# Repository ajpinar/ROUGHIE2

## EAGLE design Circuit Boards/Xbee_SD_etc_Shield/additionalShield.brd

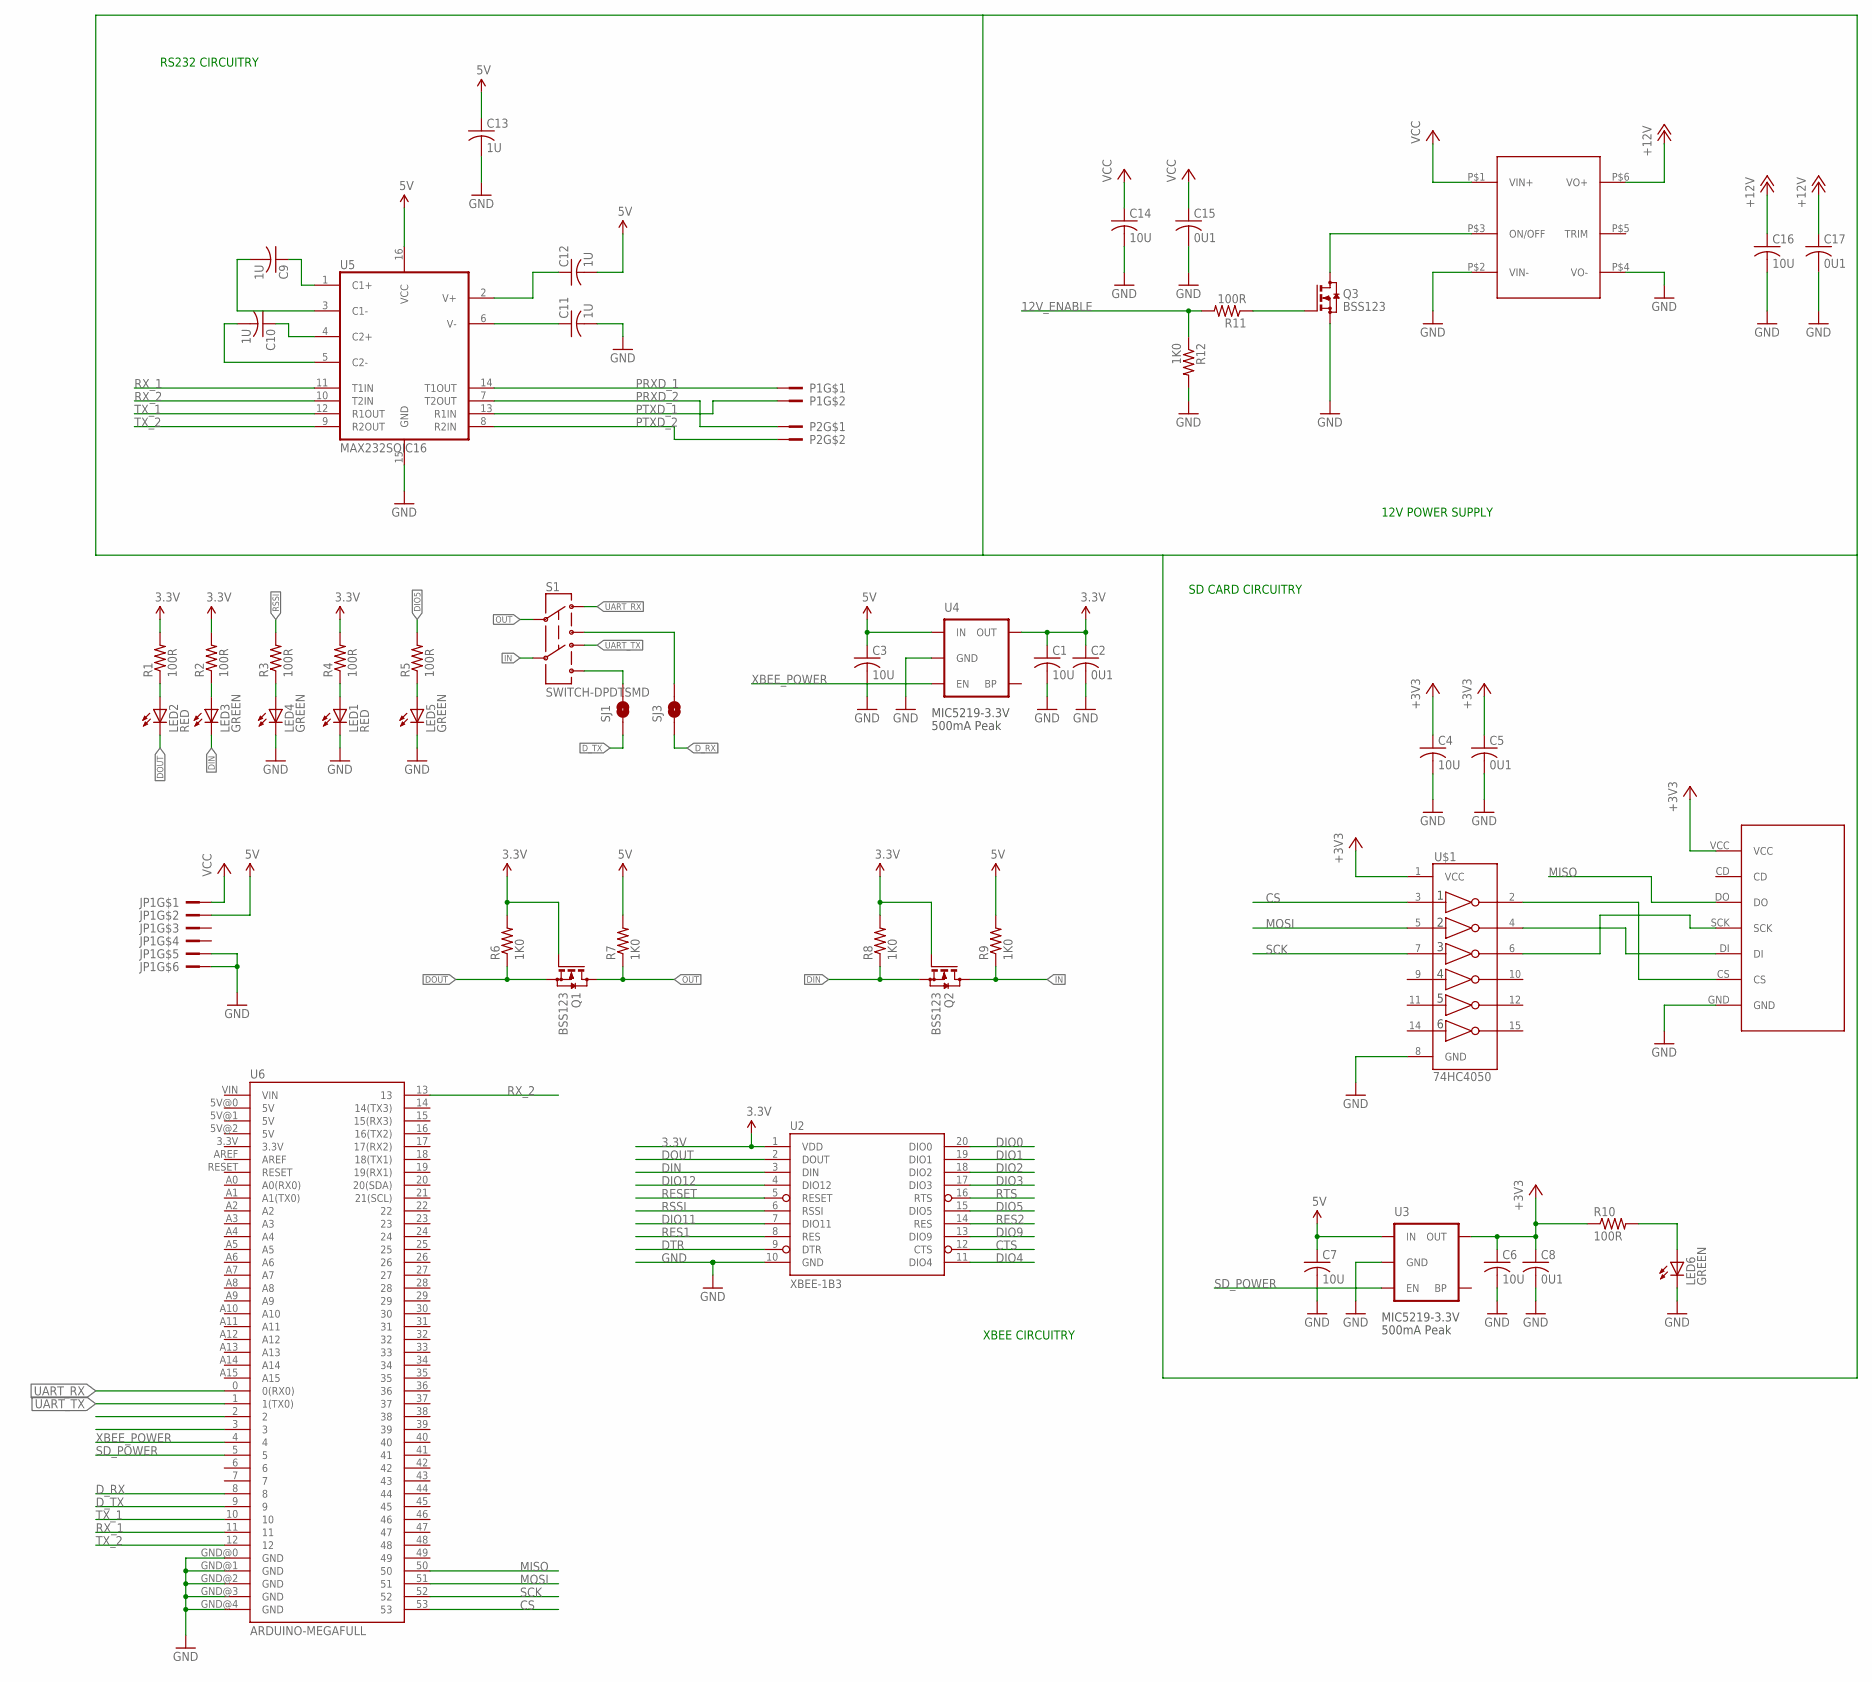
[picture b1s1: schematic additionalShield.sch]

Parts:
C1, C3, C4, C6, C7, C14, C16: 10U; C1210K
C2, C5, C8, C15, C17: 0U1; C1210K
C9, C10, C11, C12, C13: 1U; C1210K
JP1: 6PIN2ROWARDUINO
LED1, LED2: RED; CHIPLED_1206
LED3, LED4, LED5, LED6: GREEN; CHIPLED_1206
P1, P2: DF3A-2P-2DSA
Q1, Q2, Q3: BSS123; SOT23
R1, R2, R3, R4, R5, R10, R11: 100R; R1206
R6, R7, R8, R9, R12: 1K0; R1206
S1: SWITCH-DPDTSMD; AYZ0202
SJ1: D_TX; SJ_2S
SJ3: D_RX; SJ_2S
U2: XBEE-1B3; XBEE-SMD
U3, U4: V_REG_LDOSMD; SOT23-5
U5: MAX232SOIC16; SO016
U6: ARDUINO-MEGAFULL; ARDUINO_MEGA
U$1: 74HC4050; SO16
U$5: SD_BREAKOUT
U$11: SHHD001A3B41Z

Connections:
3.3V: C1.1, C2.1, Q1.1 (G), Q2.1 (G), R1.2, R2.2, R4.2, R6.2, R8.2, U2.1 (VDD), U4.5 (OUT)
5V: C3.1, C7.1, C12.2, C13.1, JP1.P$2, R7.2, R9.2, U3.1 (IN), U4.1 (IN), U5.16 (VCC)
12V_ENABLE: R11.2, R12.1
+3V3: C4.1, C5.1, C6.1, C8.1, R10.1, U3.5 (OUT), U$1.1 (VCC), U$5.VCC
+12V: C16.1, C17.1, U$11.P$6 (VO+)
CS: U6.53, U$1.3 (1A)
CTS: U2.12 (CTS)
DIN: LED3.C, Q2.2 (S), R8.1, U2.3 (DIN)
DIO0: U2.20 (DIO0)
DIO1: U2.19 (DIO1)
DIO2: U2.18 (DIO2)
DIO3: U2.17 (DIO3)
DIO4: U2.11 (DIO4)
DIO5: R5.2, U2.15 (DIO5)
DIO9: U2.13 (DIO9)
DIO11: U2.7 (DIO11)
DIO12: U2.4 (DIO12)
DOUT: LED2.C, Q1.2 (S), R6.1, U2.2 (DOUT)
DTR: U2.9 (DTR)
D_RX: SJ3.1, U6.8
D_TX: SJ1.1, U6.9
GND: C1.2, C2.2, C3.2, C4.2, C5.2, C6.2, C7.2, C8.2, C11.2, C13.2, C14.2, C15.2, C16.2, C17.2, JP1.P$5, JP1.P$6, LED1.C, LED4.C, LED5.C, LED6.C, Q3.2 (S), R12.2, U2.10 (GND), U3.2 (GND), U4.2 (GND), U5.15 (GND), U6.GND@0 (GND), U6.GND@1 (GND), U6.GND@2 (GND), U6.GND@3 (GND), U6.GND@4 (GND), U$1.8 (GND), U$5.GND, U$11.P$2 (VIN-), U$11.P$4 (VO-)
IN: Q2.3 (D), R9.1, S1.5
MISO: U6.50, U$5.DO
MOSI: U6.51, U$1.5 (2A)
unnamed: LED2.A, R1.1
unnamed: LED4.A, R3.1
unnamed: LED3.A, R2.1
unnamed: LED6.A, R10.2
unnamed: U$1.2 (1Y), U$5.CS
unnamed: U$1.4 (2Y), U$5.DI
unnamed: U$1.6 (3Y), U$5.SCK
unnamed: C9.1, U5.1 (C1+)
unnamed: C9.2, U5.3 (C1-)
unnamed: C10.1, U5.4 (C2+)
unnamed: C10.2, U5.5 (C2-)
unnamed: C11.1, U5.6 (V-)
unnamed: C12.1, U5.2 (V+)
unnamed: Q3.1 (G), R11.1
unnamed: Q3.3 (D), U$11.P$3 (ON/OFF)
unnamed: LED1.A, R4.1
unnamed: LED5.A, R5.1
unnamed: S1.6, SJ1.2
unnamed: S1.3, SJ3.2
OUT: Q1.3 (D), R7.1, S1.2
PRXD_1: P1.P$1, U5.14 (T1OUT)
PRXD_2: P2.P$1, U5.7 (T2OUT)
PTXD_1: P1.P$2, U5.13 (R1IN)
PTXD_2: P2.P$2, U5.8 (R2IN)
RES1: U2.8 (RES)
RES2: U2.14 (RES)
RESET: U2.5 (RESET)
RSSI: R3.2, U2.6 (RSSI)
RTS: U2.16 (RTS)
RX_1: U5.11 (T1IN), U6.11
RX_2: U5.10 (T2IN), U6.13
SCK: U6.52, U$1.7 (3A)
SD_POWER: U3.3 (EN), U6.5
TX_1: U5.12 (R1OUT), U6.10
TX_2: U5.9 (R2OUT), U6.12
UART_RX: S1.1, U6.0 (0(RX0))
UART_TX: S1.4, U6.1 (1(TX0))
VCC: C14.1, C15.1, JP1.P$1, U$11.P$1 (VIN+)
XBEE_POWER: U4.3 (EN), U6.4

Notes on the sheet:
500mA Peak
MIC5219-3.3V
XBEE CIRCUITRY
12V POWER SUPPLY
SD CARD CIRCUITRY
RS232 CIRCUITRY

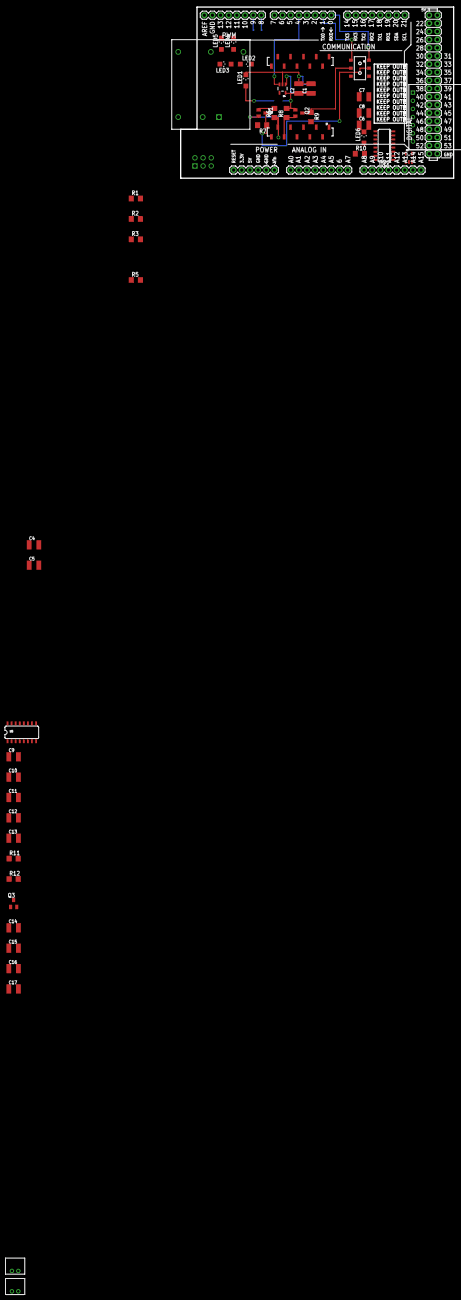
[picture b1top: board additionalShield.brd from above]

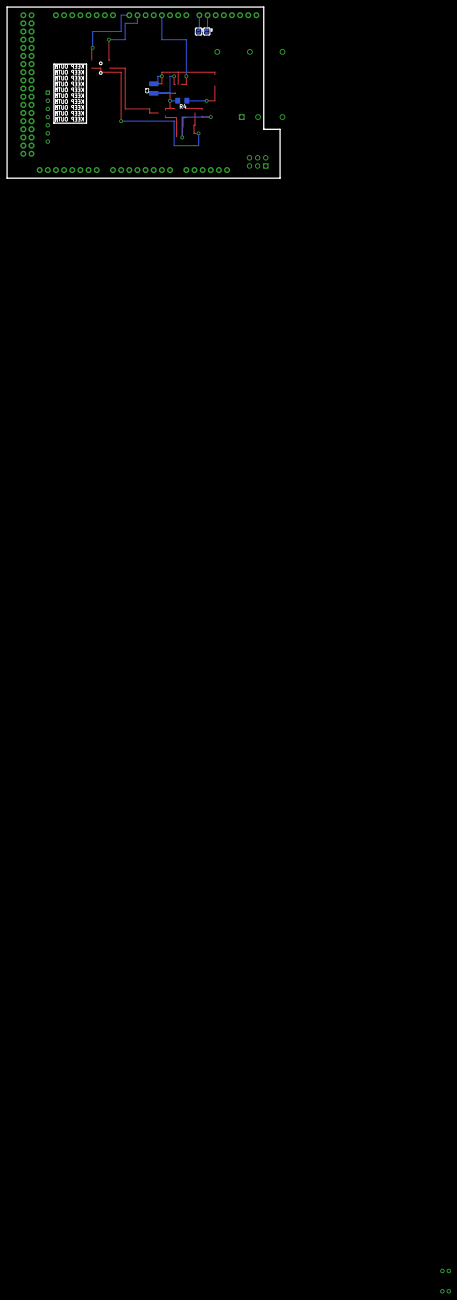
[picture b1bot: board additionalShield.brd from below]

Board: 2 copper layers, 85.1 x 53.3 mm, 52 parts (4 on the bottom side), 50 nets.

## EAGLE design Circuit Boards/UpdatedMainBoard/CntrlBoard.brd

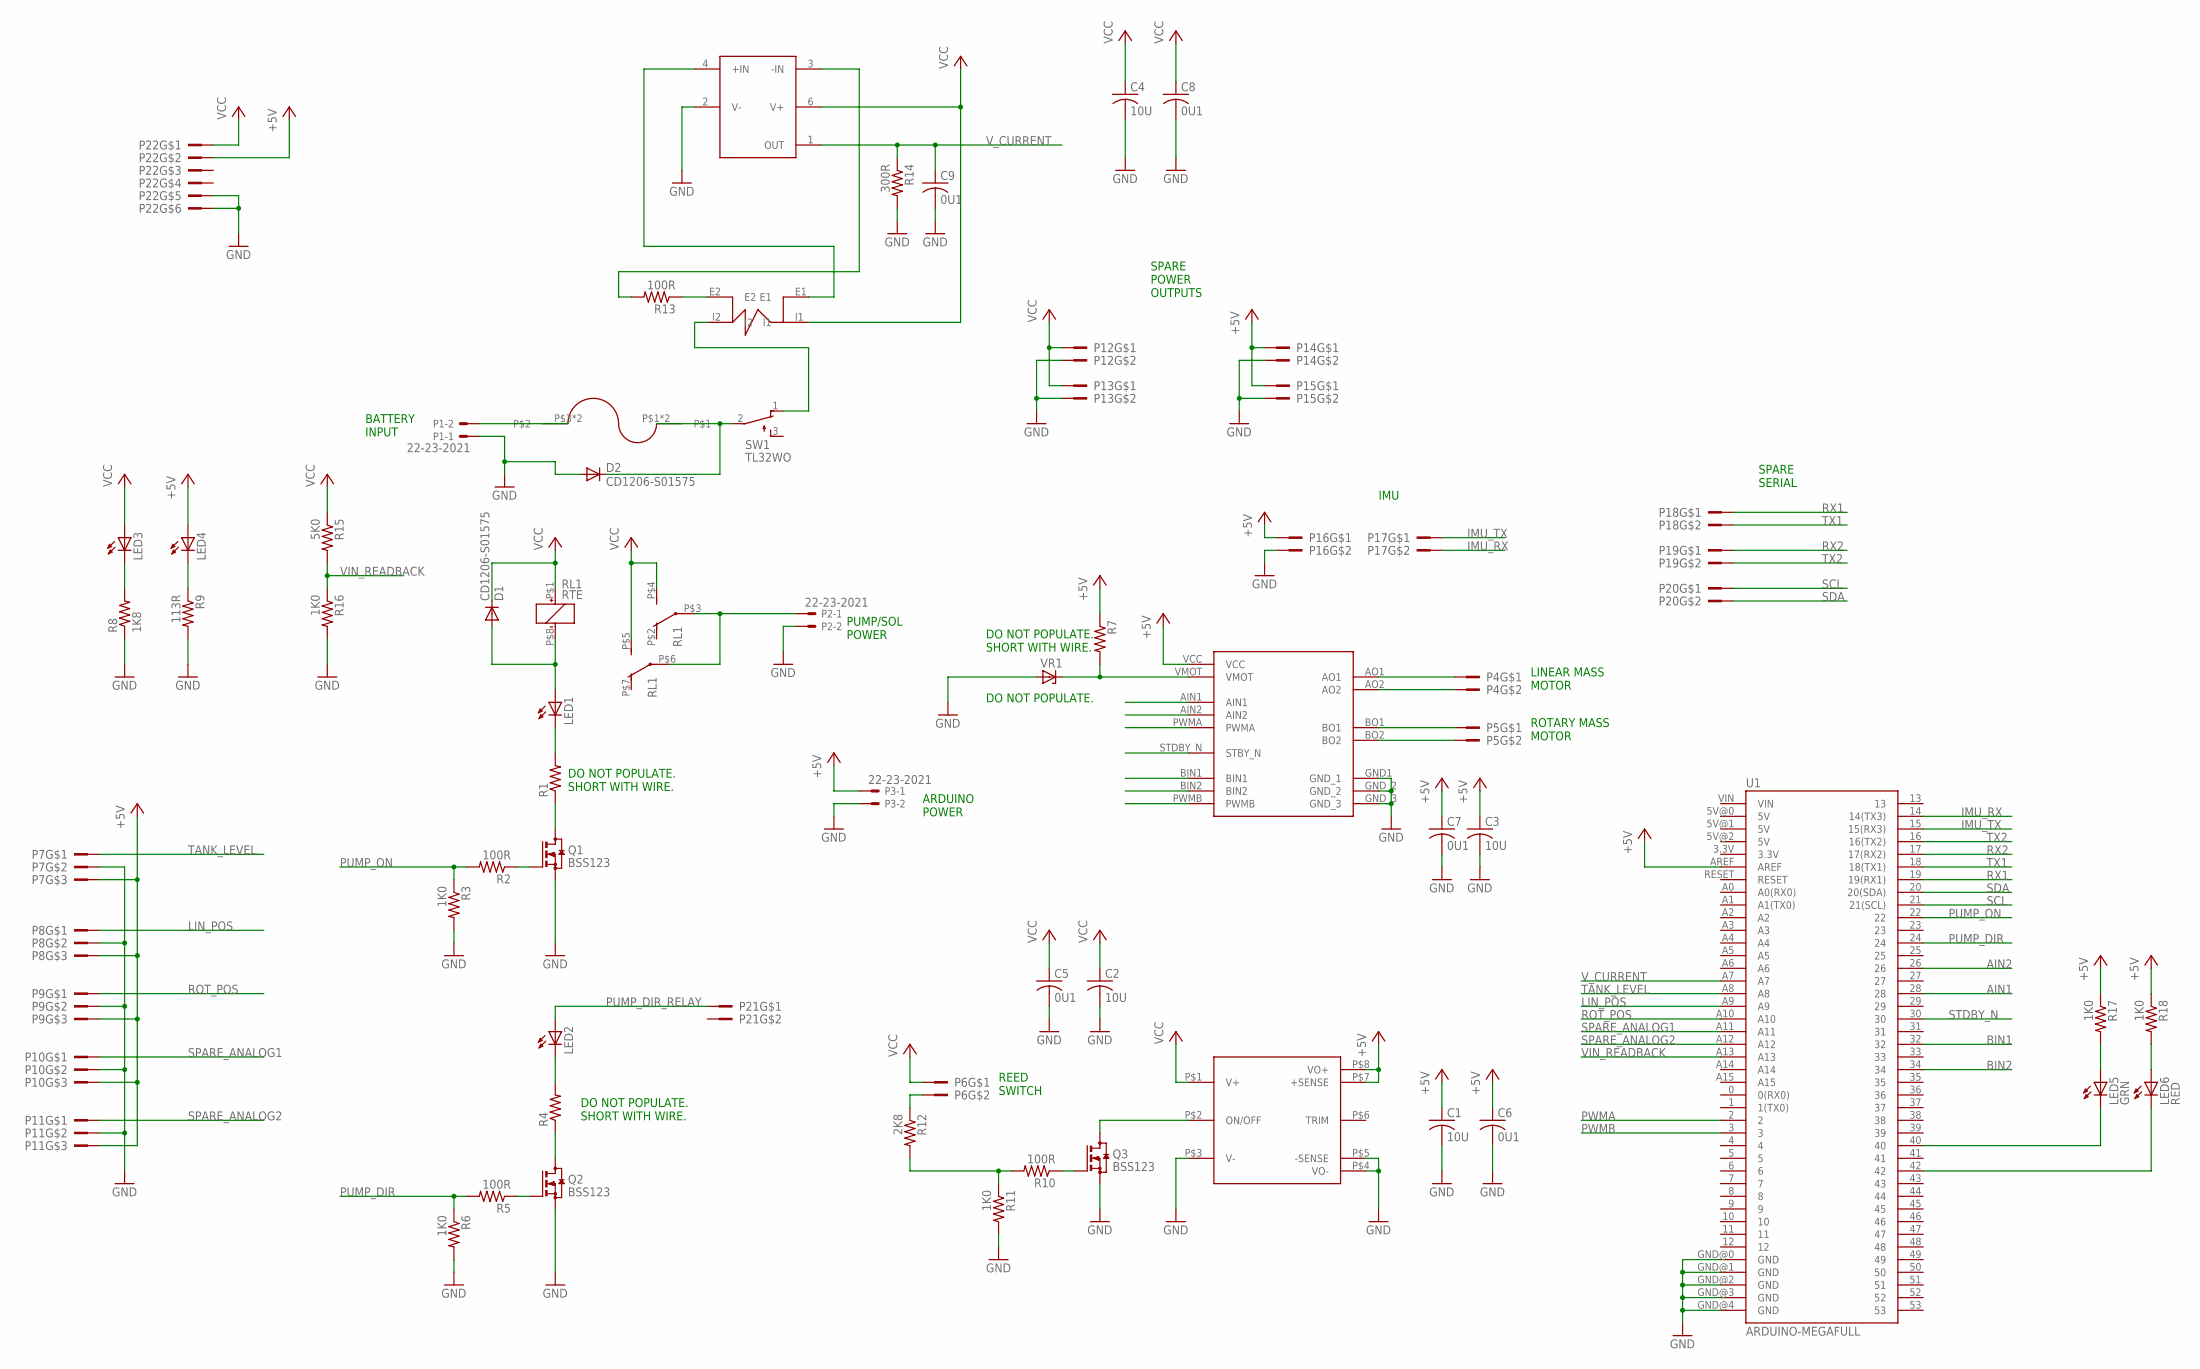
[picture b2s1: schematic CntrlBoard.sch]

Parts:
C1, C2, C3, C4: 10U; C1210K
C5, C6, C7, C8, C9: 0U1; C1210K
D1, D2: CD1206-S01575; CD1206
LED1, LED2, LED3, LED4: LEDCHIPLED_1206; CHIPLED_1206
LED5: GRN; CHIPLED_1206
LED6: RED; CHIPLED_1206
P1, P2, P3: 22-23-2021
P4, P5, P6, P12, P13, P14, P15, P16, P17, P18, P19, P20, P21: DF3A-2P-2DSA
P7, P8, P9, P10, P11: 3MM2MMLOCKING; 3PIN_2MMLOCKING
P22: 6PIN2ROWARDUINO
PS1: KHHD006A0A41Z
Q1, Q2, Q3: BSS123; SOT23
R1, R4, R7: R-US_R1206; R1206
R2, R5, R10, R13: 100R; R1206
R3, R6, R11, R16, R17, R18: 1K0; R1206
R8: 1K8; R1210
R9: 113R; R1206
R12: 2K8; R1206
R14: 300R; R1206
R15: 5K0; R1206
RL1: RTE
SW1: TL32WO; TL3XWO
U1: ARDUINO-MEGAFULL; ARDUINO_MEGA
U$1: ATC_FUSE_HOLDER; FUSE_HOLDER_ATC
U$2: POLOLU713
U$3: RSHUNT; CM2512SHUNT
U$4: LT6106; TSOT23-6
VR1: ZENER-DIODESOT23; SOT23

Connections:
+5V: C1.1, C3.1, C6.1, C7.1, LED4.A, P3.1, P7.P$3, P8.P$3, P9.P$3, P10.P$3, P11.P$3, P14.P$1, P15.P$1, P16.P$1, P22.P$2, PS1.P$7 (+SENSE), PS1.P$8 (VO+), R7.1, R17.1, R18.1, U1.AREF, U$2.VCC
AIN1: U1.28, U$2.AIN1
AIN2: U1.26, U$2.AIN2
BIN1: U1.32, U$2.BIN1
BIN2: U1.34, U$2.BIN2
GND: C1.2, C2.2, C3.2, C4.2, C5.2, C6.2, C7.2, C8.2, C9.2, D2.A, P1.1, P2.2, P3.2, P7.P$2, P8.P$2, P9.P$2, P10.P$2, P11.P$2, P12.P$2, P13.P$2, P14.P$2, P15.P$2, P16.P$2, P22.P$5, P22.P$6, PS1.P$3 (V-), PS1.P$4 (VO-), PS1.P$5 (-SENSE), Q1.2 (S), Q2.2 (S), Q3.2 (S), R3.2, R6.2, R8.1, R9.2, R11.2, R14.2, R16.2, U1.GND@0 (GND), U1.GND@1 (GND), U1.GND@2 (GND), U1.GND@3 (GND), U1.GND@4 (GND), U$2.GND1 (GND_1), U$2.GND_2, U$2.GND_3, U$4.2 (V-), VR1.1 (A)
IMU_RX: P17.P$2, U1.14 (14(TX3))
IMU_TX: P17.P$1, U1.15 (15(RX3))
LIN_POS: P8.P$1, U1.A9
unnamed: P1.2, U$1.P$3, U$1.P$4
unnamed: D1.A, LED1.A, RL1.P$8 (-)
unnamed: LED5.C, U1.40
unnamed: P2.1, RL1.P$3, RL1.P$6
unnamed: LED1.C, R1.2
unnamed: Q1.3 (D), R1.1
unnamed: Q2.3 (D), R4.1
unnamed: Q1.1 (G), R2.1
unnamed: LED2.C, R4.2
unnamed: LED4.C, R9.1
unnamed: Q2.1 (G), R5.1
unnamed: LED3.C, R8.2
unnamed: R10.2, R11.1, R12.2
unnamed: Q3.1 (G), R10.1
unnamed: P6.P$2, R12.1
unnamed: PS1.P$2 (ON/OFF), Q3.3 (D)
unnamed: P4.P$1, U$2.AO1
unnamed: P4.P$2, U$2.AO2
unnamed: P5.P$1, U$2.BO1
unnamed: P5.P$2, U$2.BO2
unnamed: R7.2, U$2.VMOT, VR1.3 (C)
unnamed: SW1.1 (O), U$3.I2
unnamed: LED6.C, U1.42
unnamed: R13.1, U$3.E2
unnamed: R13.2, U$4.3 (-IN)
unnamed: U$3.E1, U$4.4 (+IN)
unnamed: D2.K (C), SW1.2, U$1.P$1, U$1.P$2
unnamed: LED5.A, R17.2
unnamed: LED6.A, R18.2
PUMP_DIR: R5.2, R6.1, U1.24
PUMP_DIR_RELAY: LED2.A, P21.P$1
PUMP_ON: R2.2, R3.1, U1.22
PWMA: U1.2, U$2.PWMA
PWMB: U1.3, U$2.PWMB
ROT_POS: P9.P$1, U1.A10
RX1: P18.P$1, U1.19 (19(RX1))
RX2: P19.P$1, U1.17 (17(RX2))
SCL: P20.P$1, U1.21 (21(SCL))
SDA: P20.P$2, U1.20 (20(SDA))
SPARE_ANALOG1: P10.P$1, U1.A11
SPARE_ANALOG2: P11.P$1, U1.A12
STDBY_N: U1.30, U$2.STDBY_N (STBY_N)
TANK_LEVEL: P7.P$1, U1.A8
TX1: P18.P$2, U1.18 (18(TX1))
TX2: P19.P$2, U1.16 (16(TX2))
VCC: C2.1, C4.1, C5.1, C8.1, D1.K (C), LED3.A, P6.P$1, P12.P$1, P13.P$1, P22.P$1, PS1.P$1 (V+), R15.1, RL1.P$1 (+), RL1.P$4 (S), RL1.P$5 (S), U$3.I1, U$4.6 (V+)
VIN_READBACK: R15.2, R16.1, U1.A13
V_CURRENT: C9.1, R14.1, U1.A7, U$4.1 (OUT)

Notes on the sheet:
BATTERY INPUT
PUMP/SOL POWER
DO NOT POPULATE. SHORT WITH WIRE.
ARDUINO POWER
REED SWITCH
LINEAR MASS MOTOR
ROTARY MASS MOTOR
DO NOT POPULATE.
SPARE POWER OUTPUTS
IMU
SPARE SERIAL

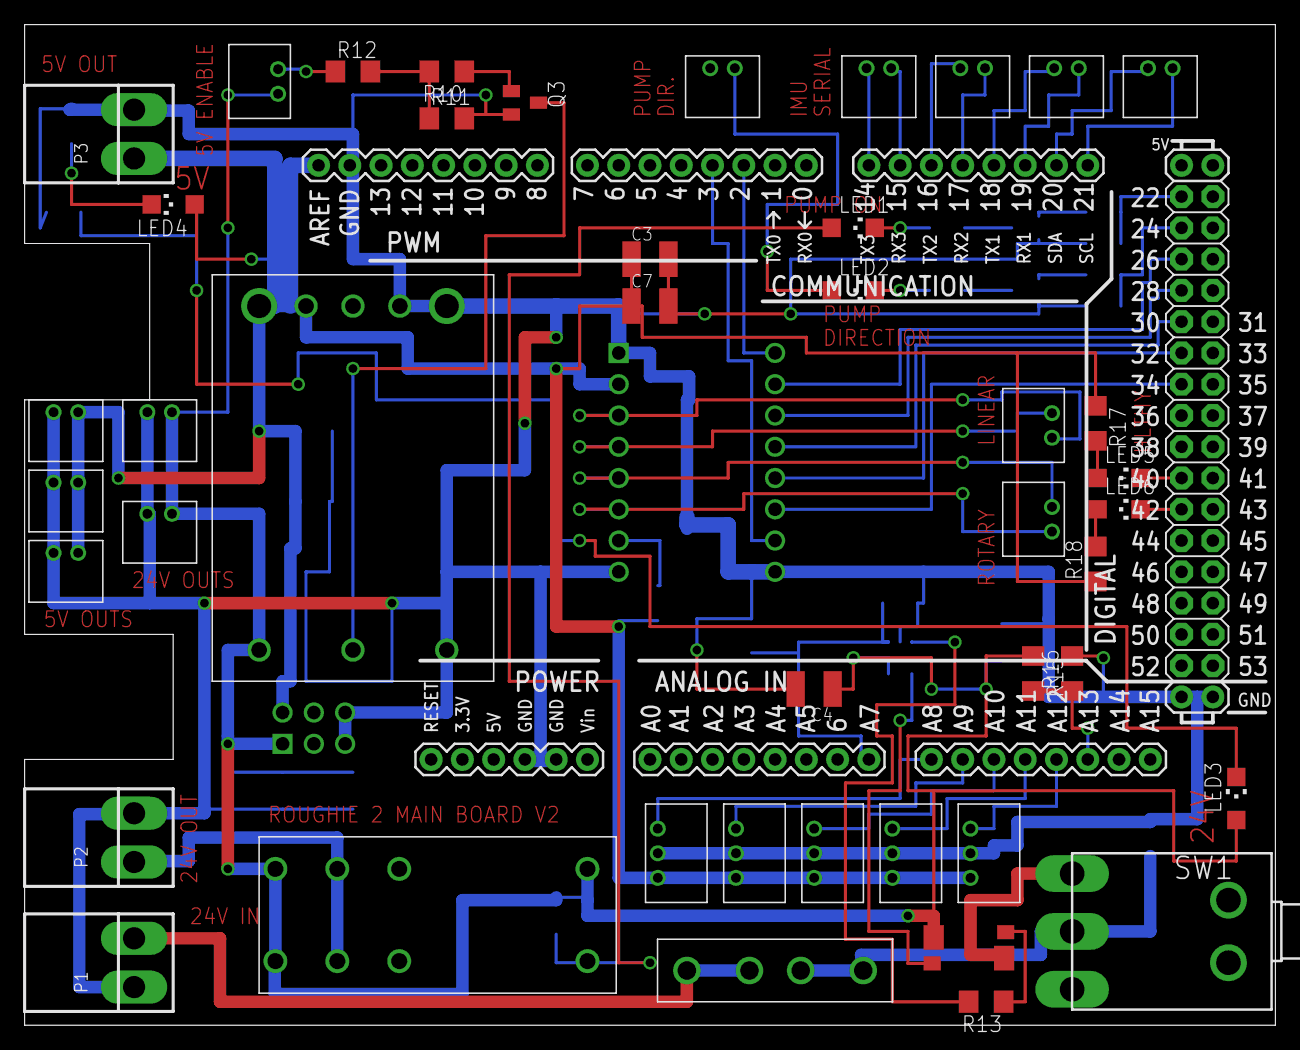
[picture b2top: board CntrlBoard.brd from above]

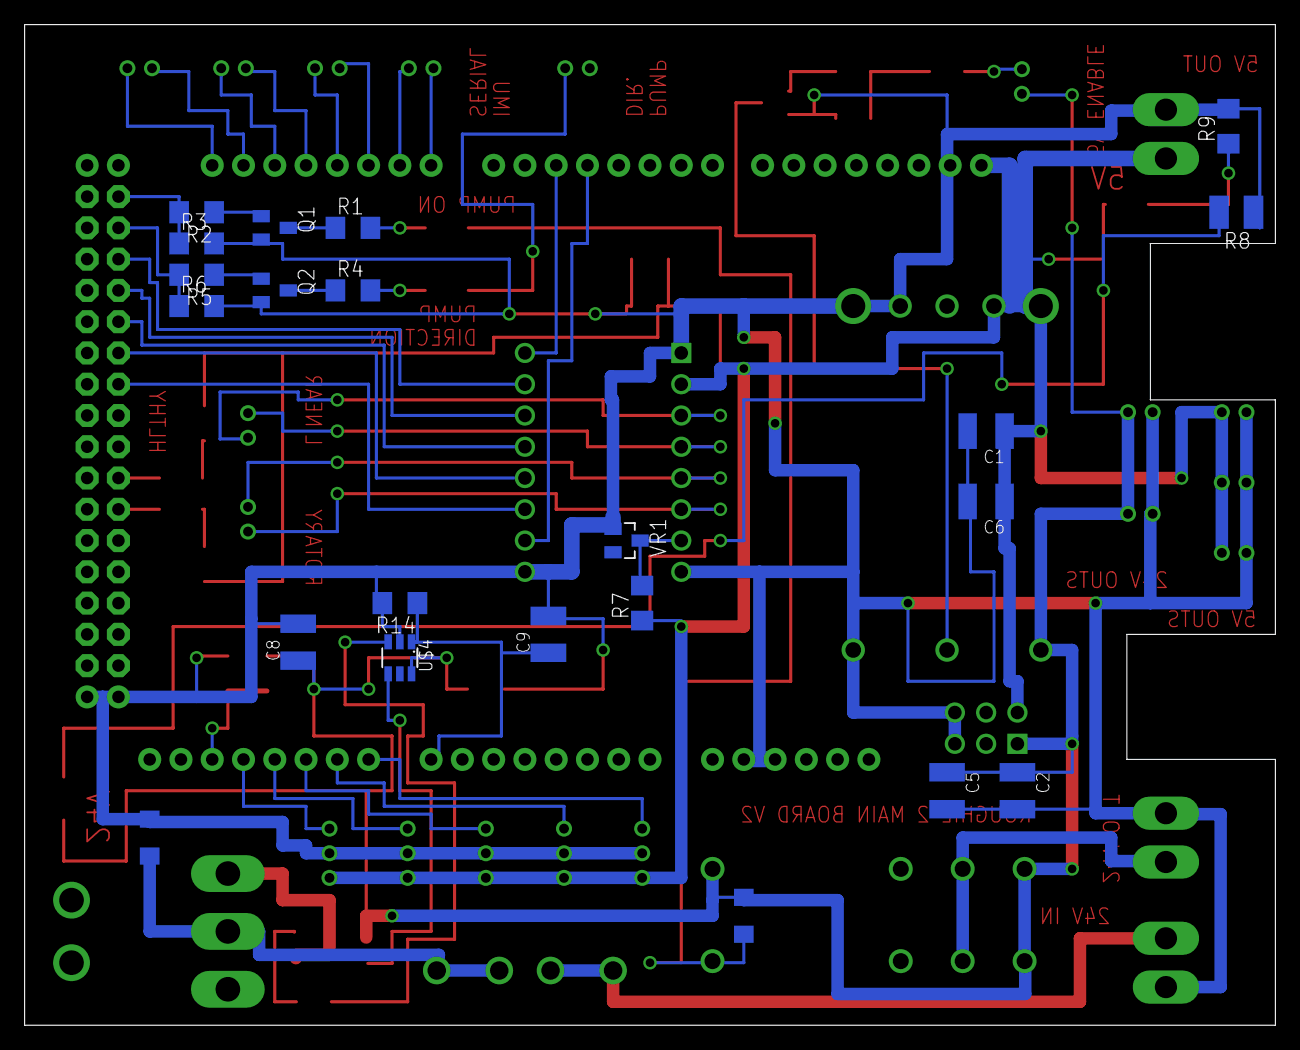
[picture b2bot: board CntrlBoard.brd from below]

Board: 2 copper layers, 101.6 x 81.3 mm, 69 parts (22 on the bottom side), 57 nets.

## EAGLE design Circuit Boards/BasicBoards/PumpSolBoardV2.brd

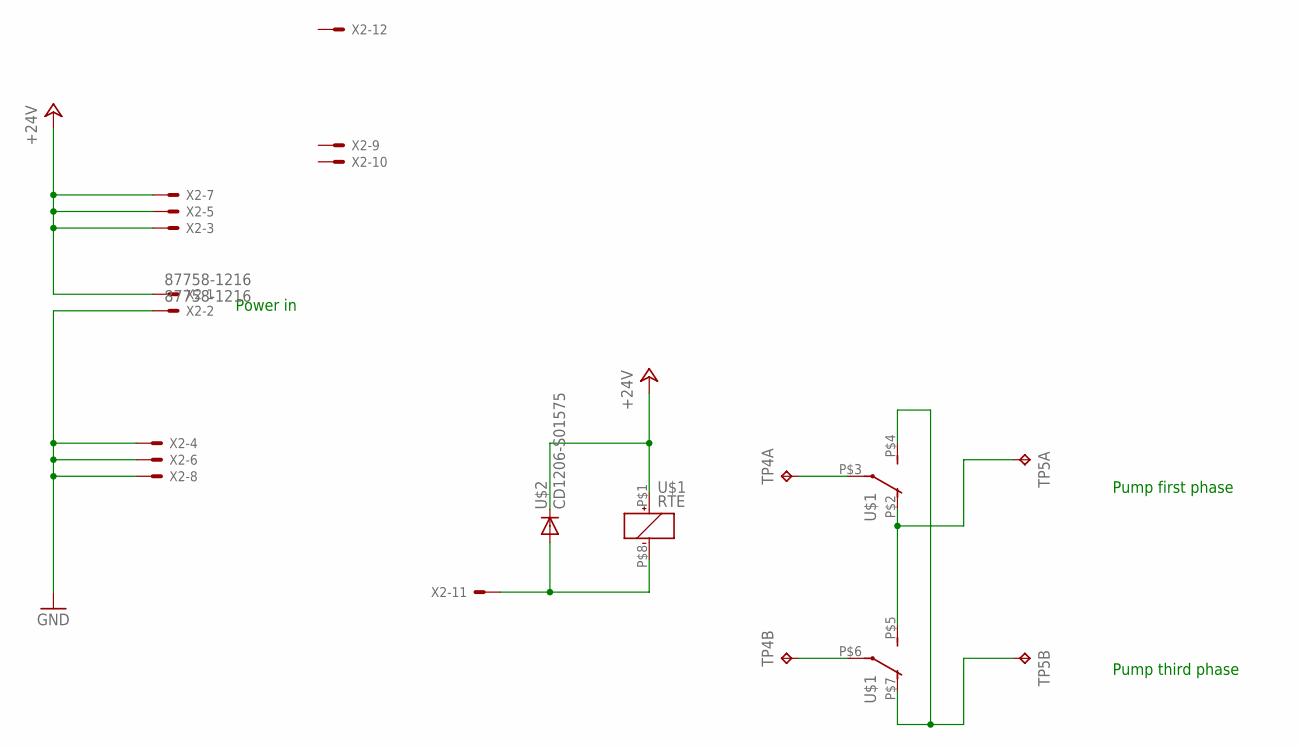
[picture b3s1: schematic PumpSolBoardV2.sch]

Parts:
TP4, TP5: TP2P2-38-20; P2-38-20
U$1: RTE
U$2: CD1206-S01575; CD1206
X2: 87758-1216

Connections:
+24V: U$1.P$1 (+), U$2.K (C), X2.1, X2.3, X2.5, X2.7
GND: X2.2, X2.4, X2.6, X2.8
unnamed: U$1.P$8 (-), U$2.A, X2.11
unnamed: TP5.TP-1, U$1.P$2 (O), U$1.P$5 (S)
unnamed: TP5.TP-2, U$1.P$4 (S), U$1.P$7 (O)
unnamed: TP4.TP-1, U$1.P$3
unnamed: TP4.TP-2, U$1.P$6

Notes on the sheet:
Pump first phase
Pump third phase
Power in

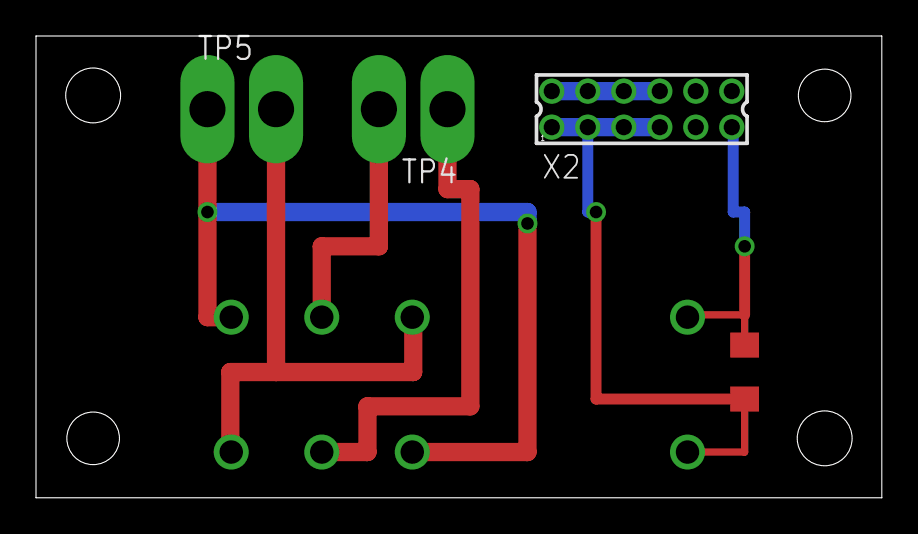
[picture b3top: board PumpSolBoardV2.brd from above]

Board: 2 copper layers, 47.0 x 25.7 mm, 5 parts (1 on the bottom side), 7 nets.

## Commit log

2015-03-24 Working code for linear P control
    Worked during pool test
2015-03-24 Rotary P control development
2015-03-25 Roll code bench tested outside of hull
    This is enough code to complete a benchtest of the roll mechanism. We
    can use it to test inside the hull when we’re ready.
2015-05-21 Made it work
2015-06-02 Updated for new circuitry
2015-06-04 Bench tested for V2 of circuitry
2015-06-04 Added Eagle files
2015-06-05 Added UpdatesToDo file
    Contains ideas for upgrades to the circuit boards
2015-06-06 Organized & started XBee
    Added new folder for updated control board development (updated control
    board is the Basic board + XBee capability & maybe other improvements
2015-06-06 Added updates 3, 4, 6, and 9 from UpdatesToDo.txt
2015-06-07 Control Board update finished
2015-06-07 Added 6 pin connector
2015-06-09 see UpdatesStillToDo.txt
2015-06-10 Updated main board again
2015-07-02 added UM7BIN
2015-07-06 added datalogging file
2015-07-07 Got SD commands fully working (no glider attached)
2015-07-09 got code working again
2015-07-16 Updated datalogging code with new linear mass limits and 3 glide cycle counter
2015-07-20 Started pressure control code
2015-07-20 minor help menu update
2015-07-21 modified timers
    Put ME_NOSE_UP and ME_NOSE_DOWN inside timers
2015-07-22 added Logs folder
2015-07-22 updated some comments in the code
2015-07-24 updated des/rise time and # cycles
2015-07-24 Added log files from Jul 23 test
2015-07-24 added 7/23 logs
2015-07-29 Added rotary benchtest code
2015-08-12 worked on rotary additions
2015-08-12 updated rotary code and verified with benchtest
2015-09-03 fixed small bugs
2015-09-03 fixed timer thing
2015-09-08 Changed code to use feedforward. Added circle trajectory code. Added GPS code.
2015-09-08 Updates from morning benchtest
2015-09-08 updated circle code
2015-09-09 Works on bench!
2015-09-13 Fixed feedforward, still needs benchtest
2015-09-17 Removed dynamical stuff and updated to use HiTec servo
2015-09-23 Added new UM7 library, gimme command, and fixed datalogger
2015-09-23 Fixed help menu
2015-09-24 Removed <3> error printout
2015-12-10 swapped roll and pitch
2016-02-01 Added vectornav crap.
2016-02-02 added pythons cript

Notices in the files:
parts and their libraries:
SparkFun-Boards: Licensing: Creative Commons ShareAlike 4.0 International - https://creativecommons.org/licenses/by-sa/4.0
SparkFun-PowerIC: Licensing: CC v3.0 Share-Alike You are welcome to use this library for commercial purposes.
